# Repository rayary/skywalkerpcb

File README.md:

skywalkerpcb
============

Schematic for Walker Electronics

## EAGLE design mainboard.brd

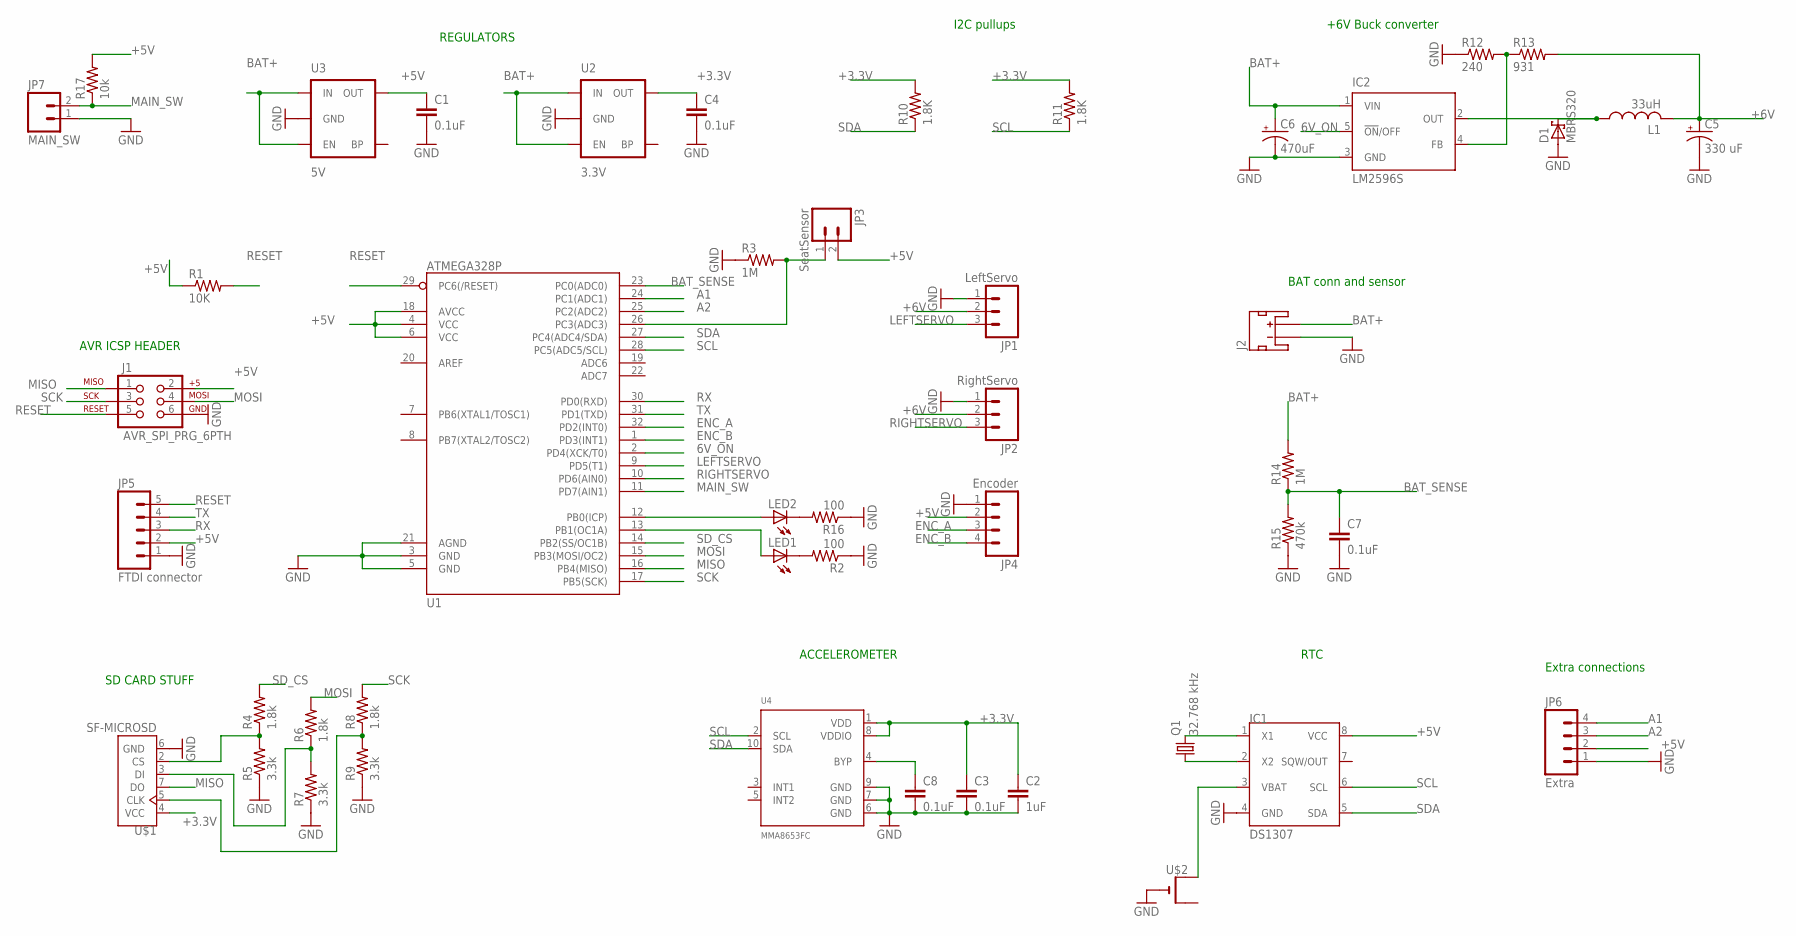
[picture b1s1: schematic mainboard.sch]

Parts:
C1, C3, C4, C7, C8: 0.1uF; 0603-CAP
C2: 1uF; 0603-CAP
C5: 330 uF; PANASONIC_E
C6: 470uF; PANASONIC_G
D1: MBRS320; SMC
IC1: DS1307; SOIC-8
IC2: LM2596S; TO263-5
J1: AVR_SPI_PRG_6PTH; 2X3
J2: JST_2MM_MALE; JST-2-SMD
JP1: LeftServo; 1X03
JP2: RightServo; 1X03
JP3: SeatSensor; 1X02
JP4: Encoder; 1X04
JP5: FTDI connector; 1X05
JP6: Extra; 1X04
JP7: MAIN_SW; 1X02
L1: 33uH; SRR1280
LED1, LED2: LED1206; LED-1206
Q1: 32.768 kHz; TC38H
R1: 10K; 0603-RES
R2, R16: 100; 0603-RES
R3, R14: 1M; 0603-RES
R4, R6, R8: 1.8k; 0603-RES
R5, R7, R9: 3.3k; 0603-RES
R10, R11: 1.8K; 0603-RES
R12: 240; 0603-RES
R13: 931; 0603-RES
R15: 470k; 0603-RES
R17: 10k; 0603-RES
U1: ATMEGA328P; TQFP32-08
U2: 3.3V; SOT23-5
U3: 5V; SOT23-5
U4: MMA8653FC; DFN10-2X2
U$1: SF-MICROSD; MICROSD
U$2: CR1220SMT; CR1220-SMD

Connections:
6V_ON: IC2.5 (!ON!/OFF), U1.2 (PD4(XCK/T0))
+3.3V: C2.1, C3.1, C4.1, R10.2, R11.2, U2.5 (OUT), U4.1 (VDD), U4.8 (VDDIO), U$1.4 (VCC)
+5V: C1.1, IC1.8 (VCC), J1.2, JP3.2, JP4.2, JP5.2, JP6.2, R1.1, R17.2, U1.4 (VCC), U1.6 (VCC), U1.18 (AVCC), U3.5 (OUT)
+6V: C5.+, JP1.2, JP2.2, L1.2, R13.2
A1: JP6.4, U1.24 (PC1(ADC1))
A2: JP6.3, U1.25 (PC2(ADC2))
BAT+: C6.+, IC2.1 (VIN), J2.2 (+), R14.2, U2.1 (IN), U2.3 (EN), U3.1 (IN), U3.3 (EN)
BAT_SENSE: C7.1, R14.1, R15.2, U1.23 (PC0(ADC0))
ENC_A: JP4.3, U1.32 (PD2(INT0))
ENC_B: JP4.4, U1.1 (PD3(INT1))
GND: C1.2, C2.2, C3.2, C4.2, C5.-, C6.-, C7.2, C8.2, D1.A, IC1.4 (GND), IC2.3 (GND), J1.6, J2.1 (-), JP1.1, JP2.1, JP4.1, JP5.1, JP6.1, JP7.1, R2.1, R3.1, R5.1, R7.1, R9.1, R12.1, R15.1, R16.1, U1.3 (GND), U1.5 (GND), U1.21 (AGND), U2.2 (GND), U3.2 (GND), U4.6 (GND), U4.7 (GND), U4.9 (GND), U$1.6 (GND), U$2.-
LEFTSERVO: JP1.3, U1.9 (PD5(T1))
MAIN_SW: JP7.2, R17.1, U1.11 (PD7(AIN1))
MISO: J1.1, U1.16 (PB4(MISO)), U$1.7 (DO)
MOSI: J1.4, R6.2, U1.15 (PB3(MOSI/OC2))
unnamed: LED1.A, U1.13 (PB1(OC1A))
unnamed: R8.1, R9.2, U$1.5 (CLK)
unnamed: R4.1, R5.2, U$1.2 (CS)
unnamed: LED1.C, R2.2
unnamed: JP3.1, R3.2, U1.26 (PC3(ADC3))
unnamed: R6.1, R7.2, U$1.3 (DI)
unnamed: IC1.3 (VBAT), U$2.+$1 (+)
unnamed: IC1.1 (X1), Q1.2
unnamed: IC1.2 (X2), Q1.1
unnamed: D1.C, IC2.2 (OUT), L1.1
unnamed: IC2.4 (FB), R12.2, R13.1
unnamed: LED2.C, R16.2
unnamed: LED2.A, U1.12 (PB0(ICP))
unnamed: C8.1, U4.4 (BYP)
RESET: J1.5, JP5.5, R1.2, U1.29 (PC6(/RESET))
RIGHTSERVO: JP2.3, U1.10 (PD6(AIN0))
RX: JP5.3, U1.30 (PD0(RXD))
SCK: J1.3, R8.2, U1.17 (PB5(SCK))
SCL: IC1.6 (SCL), R11.1, U1.28 (PC5(ADC5/SCL)), U4.2 (SCL)
SDA: IC1.5 (SDA), R10.1, U1.27 (PC4(ADC4/SDA)), U4.10 (SDA)
SD_CS: R4.2, U1.14 (PB2(SS/OC1B))
TX: JP5.4, U1.31 (PD1(TXD))

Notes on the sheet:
AVR ICSP HEADER
SD CARD STUFF
ACCELEROMETER
REGULATORS
I2C pullups
RTC
+6V Buck converter
BAT conn and sensor
Extra connections

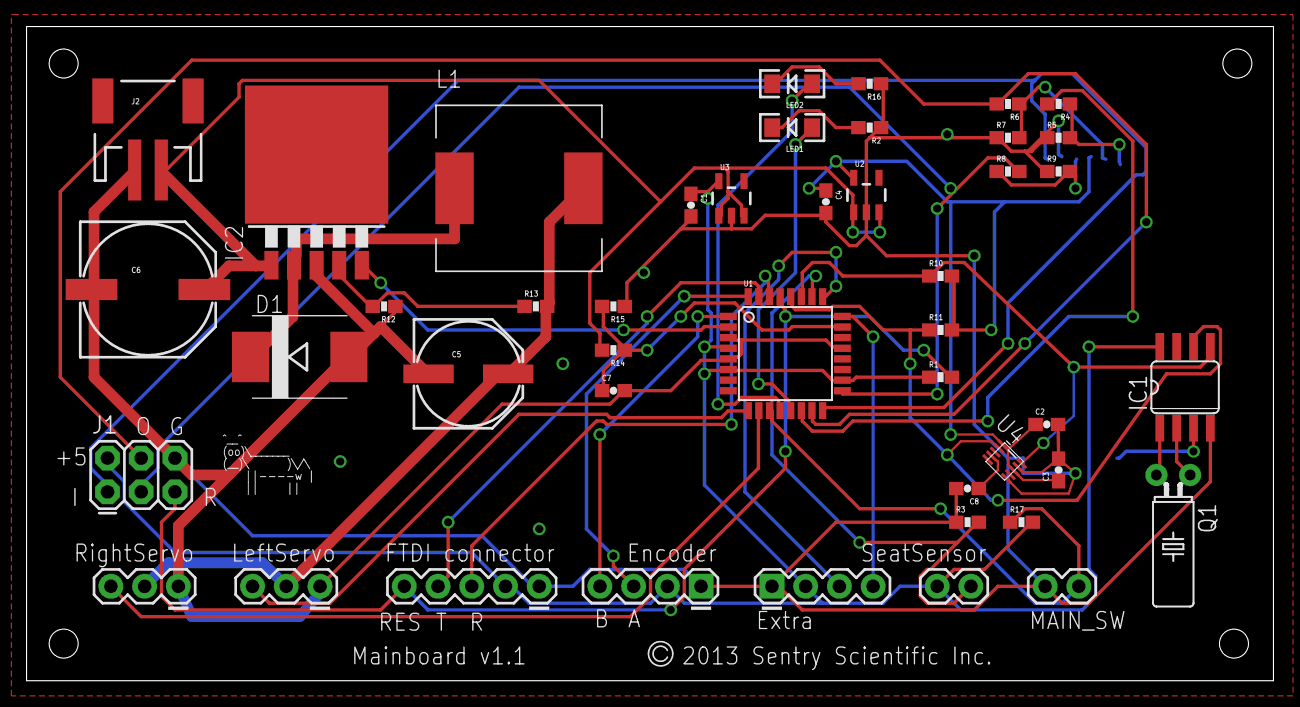
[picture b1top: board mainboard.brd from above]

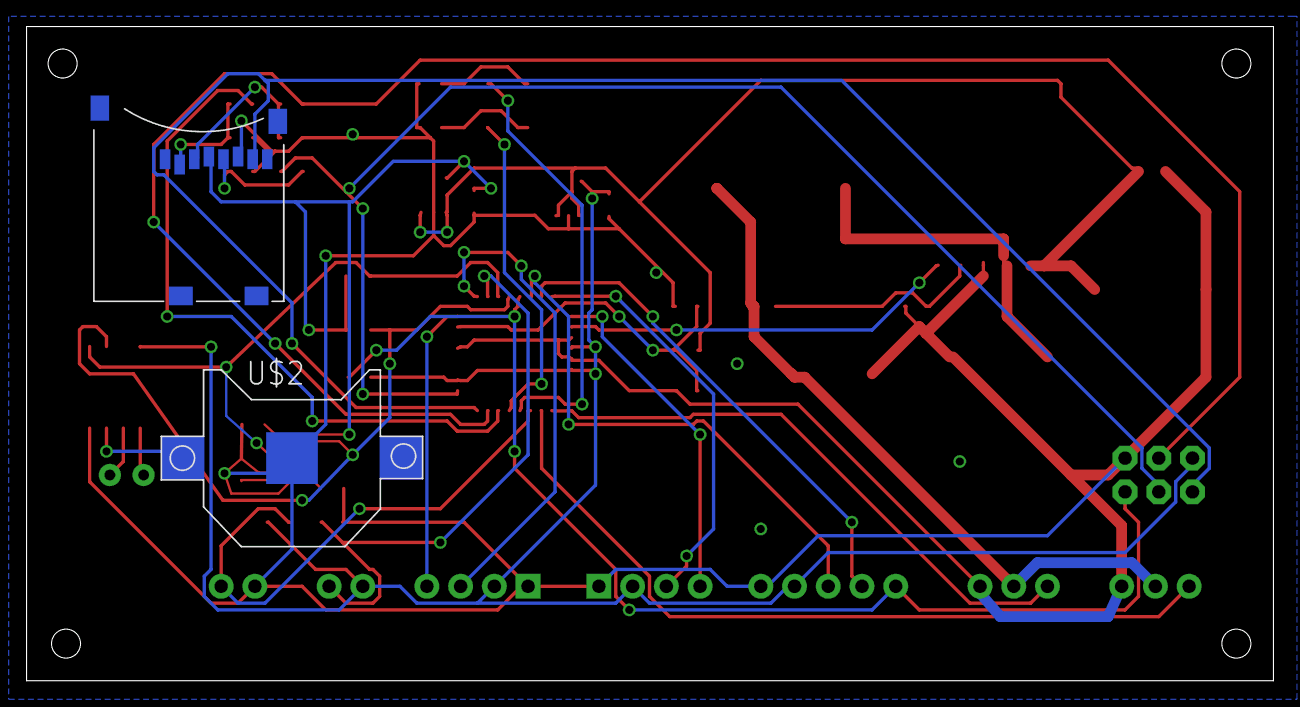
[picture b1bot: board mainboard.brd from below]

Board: 2 copper layers, 93.9 x 49.3 mm, 47 parts (2 on the bottom side), 37 nets.

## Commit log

2013-09-03 moved eagle files over from skywalker repo
2013-09-03 Added rtc
2013-09-09 Add switching regulator to board
2013-09-10 Finish 6V buck converter, add battery voltage sense
2013-09-11 Initial crack at board design
2013-09-11 Finished v1 of board design
2013-09-21 Bring it up to date
2013-10-07 Changed instances of 3.3V net to correct +3.3V net. Rerouted affected sections.
2013-10-31 added lbr for MMA8653. changed accelerometer to MMA8653.
2013-10-31 added lbr for MMA8653. switched accelerometer to MMA8653
2013-10-31 forgot files

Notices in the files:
parts and their libraries:
SparkFun-DigitalIC: Licensing: CC v3.0 Share-Alike You are welcome to use this library for commercial purposes.
